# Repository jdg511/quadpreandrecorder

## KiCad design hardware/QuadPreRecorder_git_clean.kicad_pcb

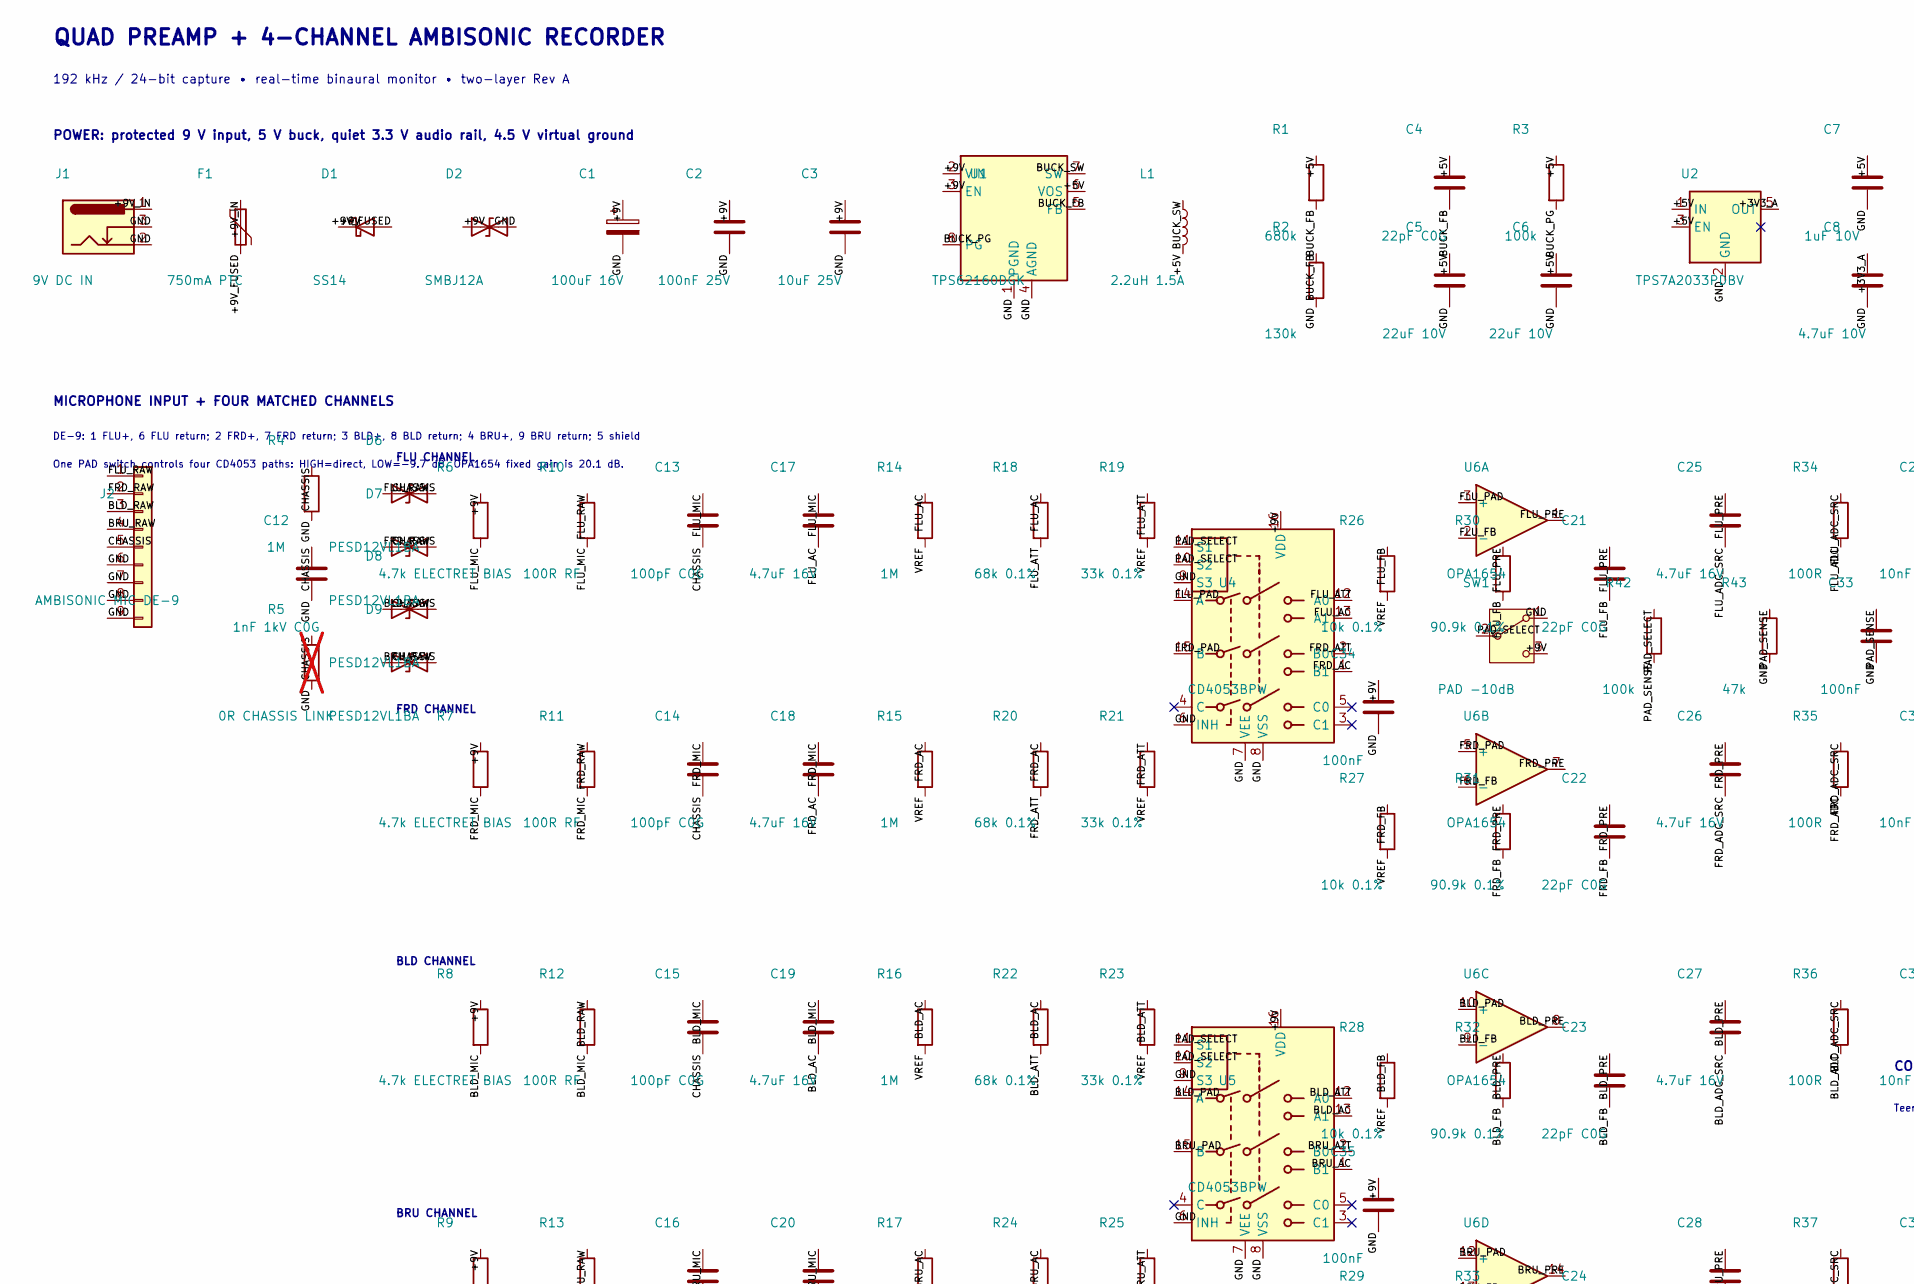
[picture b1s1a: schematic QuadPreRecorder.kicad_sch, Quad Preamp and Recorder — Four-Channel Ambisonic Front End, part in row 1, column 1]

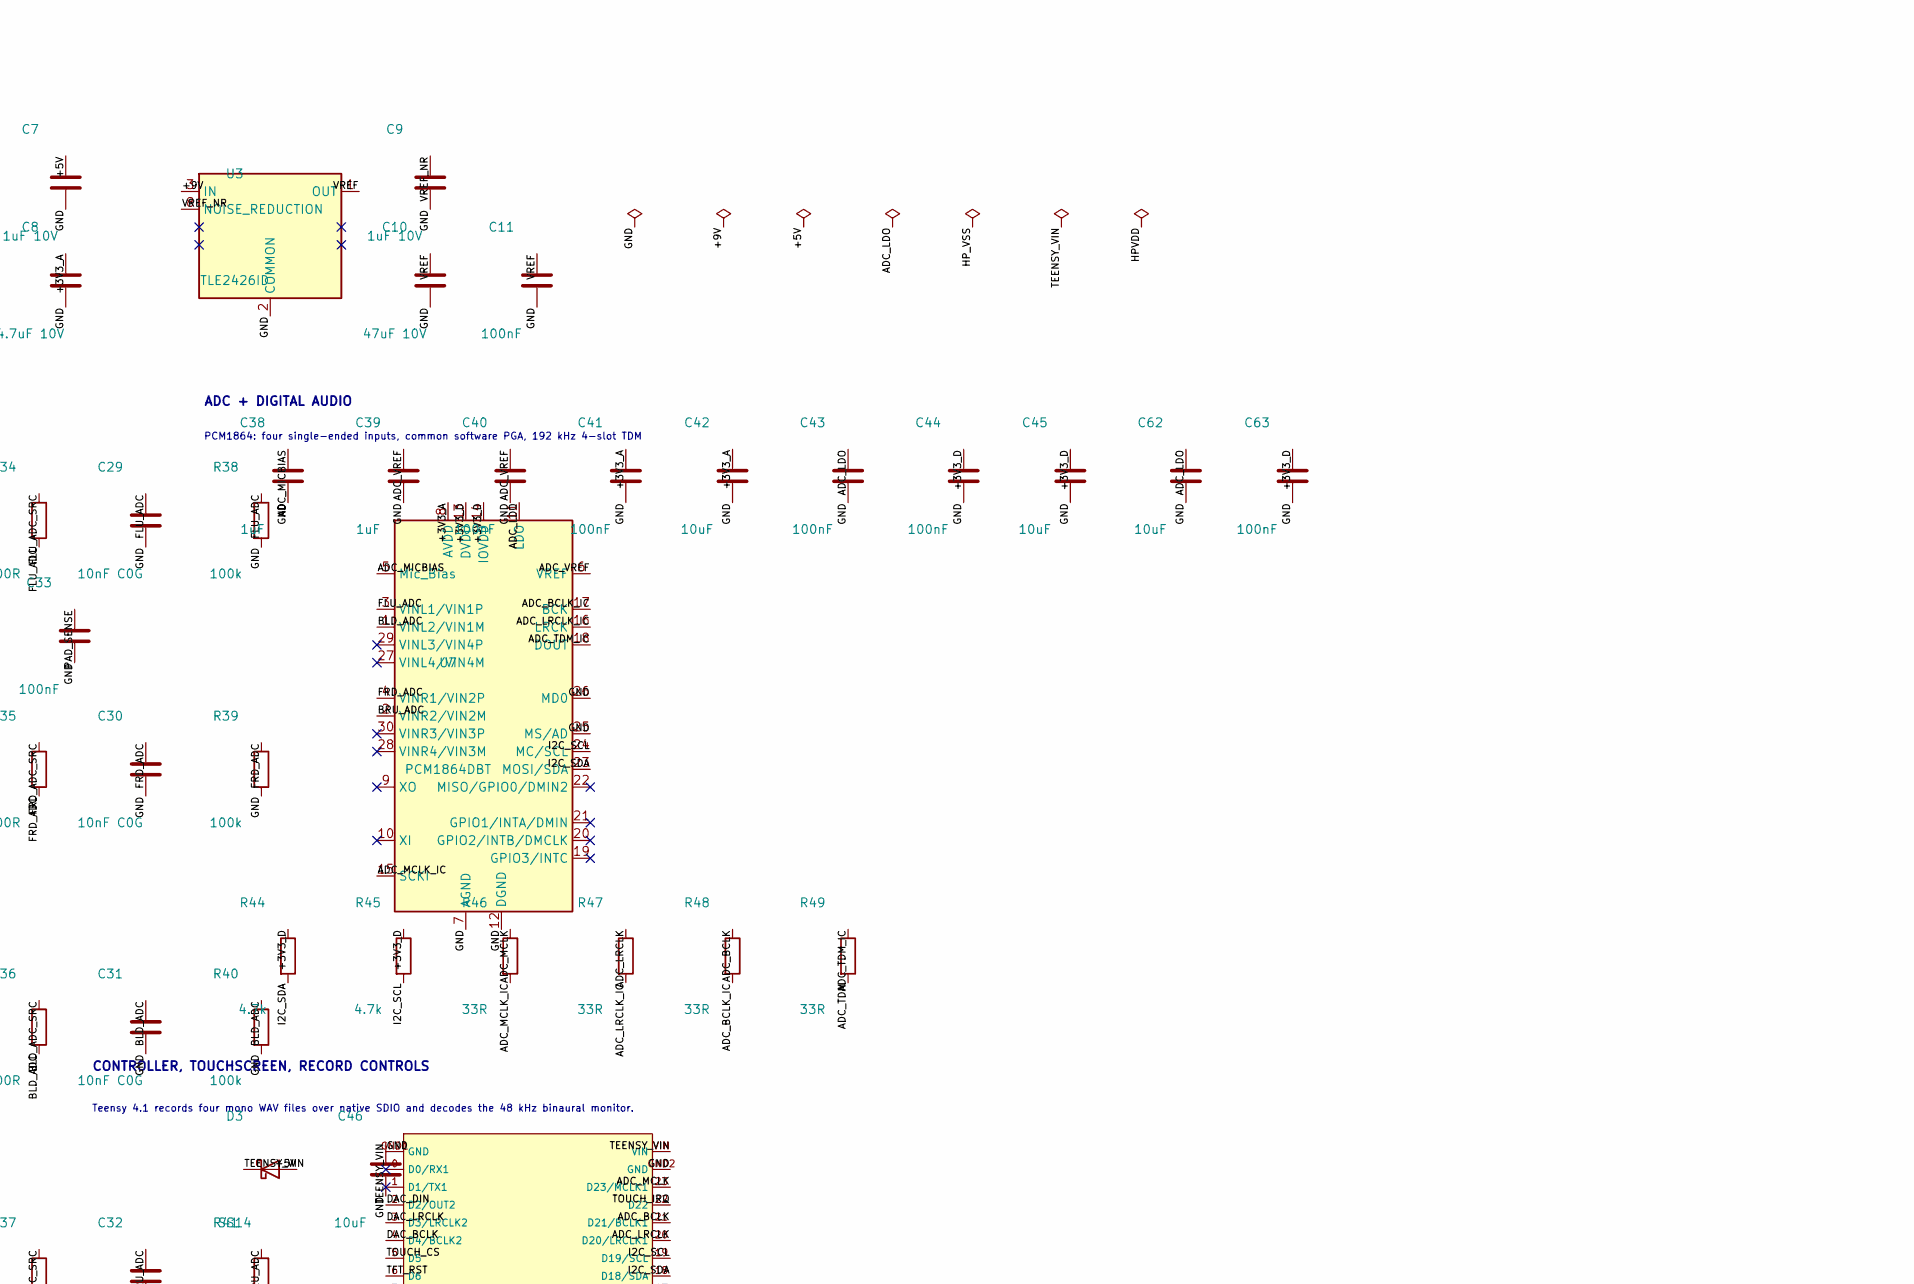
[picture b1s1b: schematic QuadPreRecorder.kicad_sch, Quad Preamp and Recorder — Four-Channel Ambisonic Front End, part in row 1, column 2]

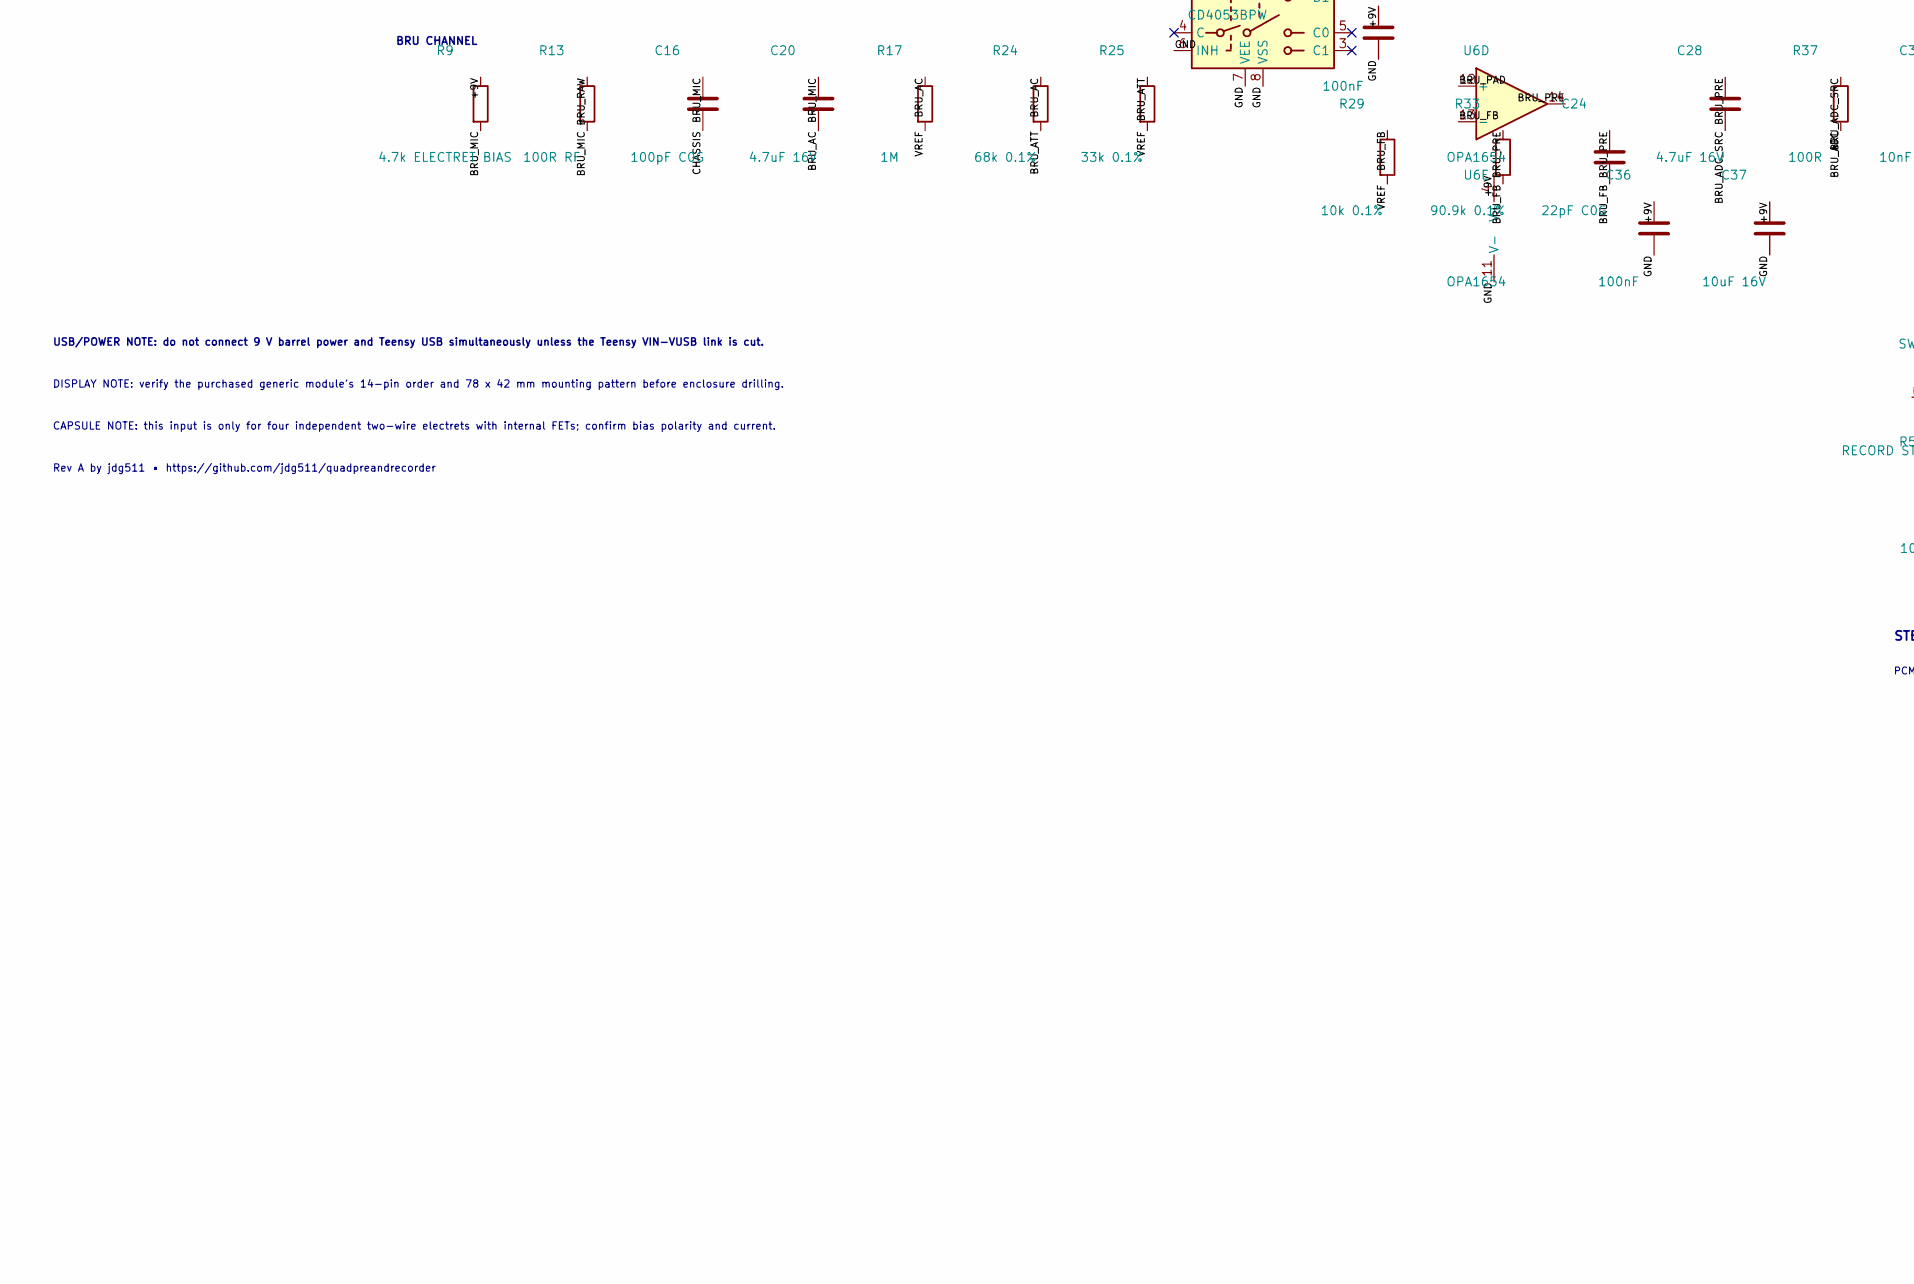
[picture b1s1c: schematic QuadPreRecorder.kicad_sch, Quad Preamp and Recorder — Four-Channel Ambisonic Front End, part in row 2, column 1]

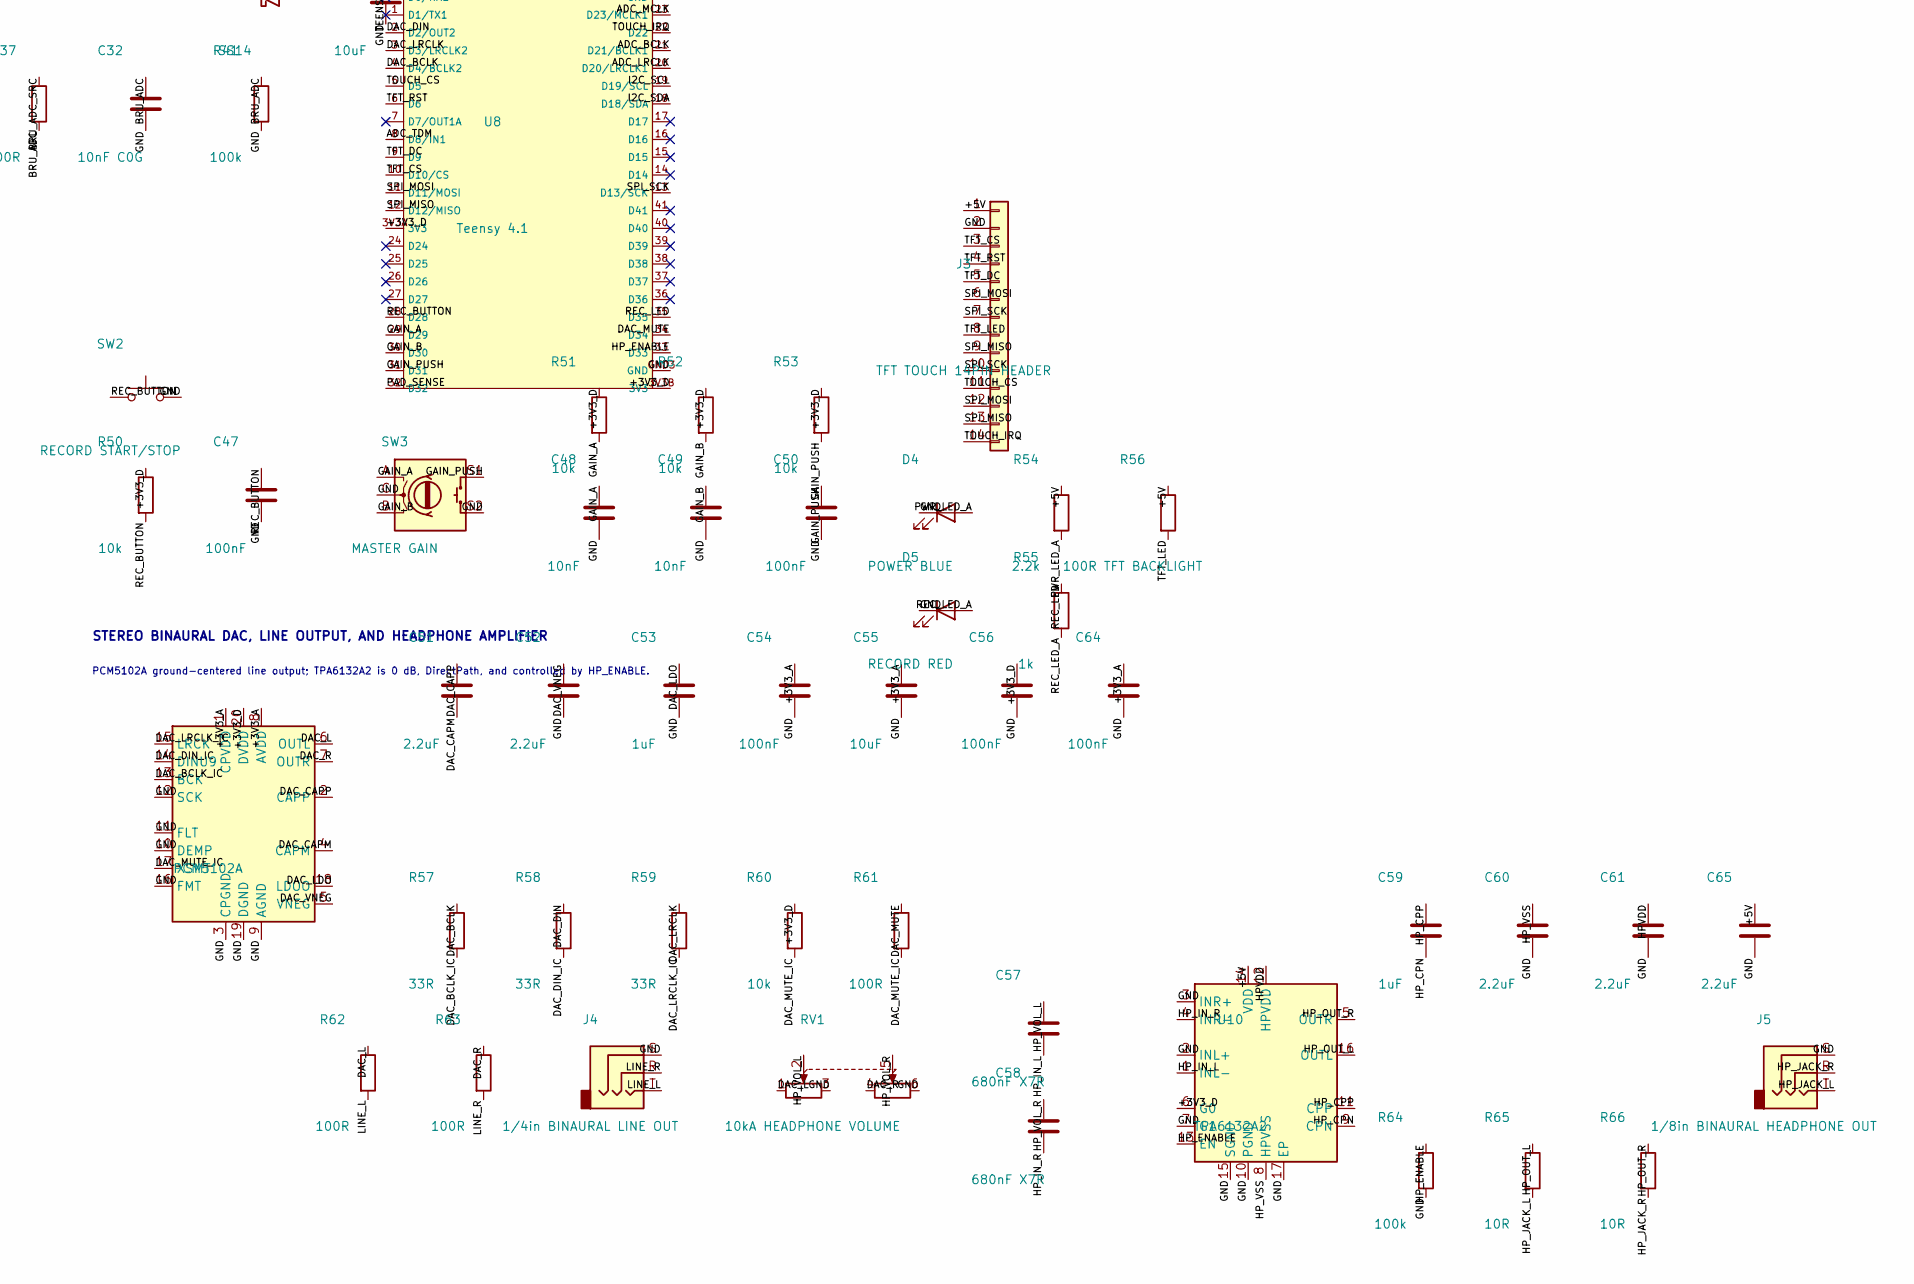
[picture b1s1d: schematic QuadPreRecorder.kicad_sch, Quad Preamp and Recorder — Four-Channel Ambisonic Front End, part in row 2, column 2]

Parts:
C1: 100uF 16V; CP_Elec_6.3x5.8; MPN EEE-FK series low-ESR aluminium electro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
C2: 100nF 25V; C_0805_2012Metric; MPN GRM series X7R/C0G
C3: 10uF 25V; C_1206_3216Metric; MPN GRM series X7R/C0G
C4, C21, C22, C23, C24: 22pF C0G; C_0603_1608Metric; MPN GRM series X7R/C0G
C5, C6: 22uF 10V; C_1206_3216Metric; MPN GRM series X7R/C0G
C7, C9: 1uF 10V; C_0805_2012Metric; MPN GRM series X7R/C0G
C8: 4.7uF 10V; C_0805_2012Metric; MPN GRM series X7R/C0G
C10: 47uF 10V; C_1206_3216Metric; MPN GRM series X7R/C0G
C11, C33, C34, C35, C36, C40, C41, C43, C44, C47, C50, C54, C56, C63, C64: 100nF; C_0603_1608Metric; MPN GRM series X7R/C0G
C12: 1nF 1kV C0G; C_0805_2012Metric; MPN GRM series X7R/C0G
C13, C14, C15, C16: 100pF C0G; C_0603_1608Metric; MPN GRM series X7R/C0G
C17, C18, C19, C20, C25, C26, C27, C28: 4.7uF 16V; C_1206_3216Metric; MPN GRM series X7R/C0G
C29, C30, C31, C32: 10nF C0G; C_0603_1608Metric; MPN GRM series X7R/C0G
C37: 10uF 16V; C_1206_3216Metric; MPN GRM series X7R/C0G
C38, C39, C53, C59: 1uF; C_0805_2012Metric; MPN GRM series X7R/C0G
C42, C45, C46, C55, C62: 10uF; C_1206_3216Metric; MPN GRM series X7R/C0G
C48, C49: 10nF; C_0603_1608Metric; MPN GRM series X7R/C0G
C51, C52, C60, C61, C65: 2.2uF; C_0805_2012Metric; MPN GRM series X7R/C0G
C57, C58: 680nF X7R; C_0805_2012Metric; MPN GRM series X7R/C0G
D1, D3: SS14; D_SMA; MPN SS14-13-F
D2: SMBJ12A; D_SMB; MPN SMBJ12A
D4: POWER BLUE; LED_0603_1608Metric; MPN LTST-C190TBKT
D5: RECORD RED; LED_0603_1608Metric; MPN LTST-C190KRKT
D6, D7, D8, D9: PESD12VL1BA; D_SOD-323; MPN PESD12VL1BA,115
F1: 750mA PTC; Fuse_1206_3216Metric; MPN 1206L075/13.2WR
J1: 9V DC IN; BarrelJack_CUI_PJ-102AH_Horizontal; MPN PJ-102AH
J2: AMBISONIC MIC DE-9; DSUB-9_Socket_Horizontal_P2.77x2.84mm_EdgePinOffset9.40mm; MPN LD09S13A4GV00LF
J3: TFT TOUCH 14PIN HEADER; PinHeader_1x14_P2.54mm_Vertical; MPN PRPC014SAAN-RC
J4: 1/4in BINAURAL LINE OUT; Jack_6.35mm_Neutrik_NRJ6HF_Horizontal; MPN NRJ6HF
J5: 1/8in BINAURAL HEADPHONE OUT; Jack_3.5mm_CUI_SJ1-3533NG_Horizontal; MPN SJ1-3533NG
L1: 2.2uH 1.5A; L_Abracon_ASPIAIG-F4020; MPN ASPIAIG-F4020-2R2M-T
R1: 680k; R_0603_1608Metric; MPN RC0603FR series, 1%
R2: 130k; R_0603_1608Metric; MPN RC0603FR series, 1%
R3, R38, R39, R40, R41, R42, R64: 100k; R_0603_1608Metric; MPN RC0603FR series, 1%
R4, R14, R15, R16, R17: 1M; R_0603_1608Metric; MPN RC0603FR series, 1%
R5: 0R CHASSIS LINK; R_0603_1608Metric; MPN RC0603FR series, 1%; not fitted
R6, R7, R8, R9: 4.7k ELECTRET BIAS; R_0603_1608Metric; MPN RC0603FR series, 1%
R10, R11, R12, R13: 100R RF; R_0603_1608Metric; MPN RC0603FR series, 1%
R18, R20, R22, R24: 68k 0.1%; R_0603_1608Metric; MPN TNPW0603 series, 0.1%
R19, R21, R23, R25: 33k 0.1%; R_0603_1608Metric; MPN TNPW0603 series, 0.1%
R26, R27, R28, R29: 10k 0.1%; R_0603_1608Metric; MPN TNPW0603 series, 0.1%
R30, R31, R32, R33: 90.9k 0.1%; R_0603_1608Metric; MPN TNPW0603 series, 0.1%
R34, R35, R36, R37, R61, R62, R63: 100R; R_0603_1608Metric; MPN RC0603FR series, 1%
R43: 47k; R_0603_1608Metric; MPN RC0603FR series, 1%
R44, R45: 4.7k; R_0603_1608Metric; MPN RC0603FR series, 1%
R46, R47, R48, R49, R57, R58, R59: 33R; R_0603_1608Metric; MPN RC0603FR series, 1%
R50, R51, R52, R53, R60: 10k; R_0603_1608Metric; MPN RC0603FR series, 1%
R54: 2.2k; R_0603_1608Metric; MPN RC0603FR series, 1%
R55: 1k; R_0603_1608Metric; MPN RC0603FR series, 1%
R56: 100R TFT BACKLIGHT; R_0805_2012Metric; MPN RC0805FR-07100RL
R65, R66: 10R; R_0603_1608Metric; MPN RC0603FR series, 1%
RV1: 10kA HEADPHONE VOLUME; RK097_Dual_Horizontal_NoEdgeGuide; MPN RK0971221-F15-C0-A103
SW1: PAD -10dB; SW_Slide_SPDT_Straight_CK_OS102011MS2Q; MPN OS102011MS2QN1
SW2: RECORD START/STOP; SW_PUSH-12mm; MPN B3F-4050
SW3: MASTER GAIN; RotaryEncoder_Alps_EC11E-Switch_Vertical_H20mm; MPN EC11E15244G1
U1: TPS62160DGK; VSSOP-8_3x3mm_P0.65mm; MPN TPS62160DGKR
U2: TPS7A2033PDBV; SOT-23-5; MPN TPS7A2033PDBVR
U3: TLE2426ID; SOIC-8_3.9x4.9mm_P1.27mm; MPN TLE2426IDR
U4, U5: CD4053BPW; TSSOP-16_4.4x5mm_P0.65mm; MPN CD4053BPWR
U6: OPA1654; TSSOP-14_4.4x5mm_P0.65mm; MPN OPA1654AIPWR
U7: PCM1864DBT; TSSOP-30_4.4x7.8mm_P0.5mm; MPN PCM1864DBTR
U8: Teensy 4.1; Teensy41_Socket; MPN TEENSY41
U9: PCM5102A; TSSOP-20_4.4x6.5mm_P0.65mm; MPN PCM5102APWR
U10: TPA6132A2; WQFN-16-1EP_3x3mm_P0.5mm_EP1.6x1.6mm; MPN TPA6132A2RTER

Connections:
/+3V3_A: C8.1, C41.1, C42.1, C54.1, C55.1, C64.1, U2.5 (OUT), U7.8 (AVDD), U9.1 (CPVDD), U9.8 (AVDD)
/+3V3_D: C44.1, C45.1, C56.1, C63.1, R44.1, R45.1, R50.1, R51.1, R52.1, R53.1, R60.1, U7.13 (DVDD), U7.14 (IOVDD), U8.3V3A (3V3), U8.3V3B (3V3), U9.20 (DVDD), U10.6 (G0)
/+5V: C4.1, C5.1, C6.1, C7.1, C65.1, D3.2 (A), J3.1, L1.2, R1.1, R3.1, R54.1, R56.1, U1.6 (VOS), U2.1 (IN), U2.3 (EN), U10.14 (VDD)
/+9V: C1.1, C2.1, C3.1, C34.1, C35.1, C36.1, C37.1, D1.1 (K), D2.1 (A1), R6.1, R7.1, R8.1, R9.1, SW1.3 (C), U1.2 (VIN), U1.3 (EN), U3.3 (IN), U4.16 (VDD), U5.16 (VDD), U6.4 (V+)
/+9V_FUSED: D1.2 (A), F1.2
/+9V_IN: F1.1, J1.1
/ADC_BCLK: R48.1, U8.21 (D21/BCLK1)
/ADC_BCLK_IC: R48.2, U7.17 (BCK)
/ADC_LDO: C43.1, C62.1, U7.11 (LDO)
/ADC_LRCLK: R47.1, U8.20 (D20/LRCLK1)
/ADC_LRCLK_IC: R47.2, U7.16 (LRCK)
/ADC_MCLK: R46.1, U8.23 (D23/MCLK1)
/ADC_MCLK_IC: R46.2, U7.15 (SCKI)
/ADC_MICBIAS: C38.1, U7.5 (Mic_Bias)
/ADC_TDM: R49.2, U8.8 (D8/IN1)
/ADC_TDM_IC: R49.1, U7.18 (DOUT)
/ADC_VREF: C39.1, C40.1, U7.6 (VREF)
/BLD_AC: C19.2, R16.1, R22.1, U5.13 (A1)
/BLD_ADC: C31.1, R36.2, R40.1, U7.1 (VINL2/VIN1M)
/BLD_ADC_SRC: C27.2, R36.1
/BLD_ATT: R22.2, R23.1, U5.12 (A0)
/BLD_FB: C23.2, R28.1, R32.2, U6.9 (-)
/BLD_MIC: C15.1, C19.1, R8.2, R12.2
/BLD_PAD: U5.14 (A), U6.10 (+)
/BLD_PRE: C23.1, C27.1, R32.1, U6.8
/BLD_RAW: D8.1 (A1), J2.3, R12.1
/BRU_AC: C20.2, R17.1, R24.1, U5.1 (B1)
/BRU_ADC: C32.1, R37.2, R41.1, U7.2 (VINR2/VIN2M)
/BRU_ADC_SRC: C28.2, R37.1
/BRU_ATT: R24.2, R25.1, U5.2 (B0)
/BRU_FB: C24.2, R29.1, R33.2, U6.13 (-)
/BRU_MIC: C16.1, C20.1, R9.2, R13.2
/BRU_PAD: U5.15 (B), U6.12 (+)
/BRU_PRE: C24.1, C28.1, R33.1, U6.14
/BRU_RAW: D9.1 (A1), J2.4, R13.1
/BUCK_FB: C4.2, R1.2, R2.1, U1.5 (FB)
/BUCK_PG: R3.2, U1.8 (PG)
/BUCK_SW: L1.1, U1.7 (SW)
/CHASSIS: C12.1, C13.2, C14.2, C15.2, C16.2, D6.2 (A2), D7.2 (A2), D8.2 (A2), D9.2 (A2), J2.5, R4.1, R5.1
/DAC_BCLK: R57.1, U8.4 (D4/BCLK2)
/DAC_BCLK_IC: R57.2, U9.13 (BCK)
/DAC_CAPM: C51.2, U9.4 (CAPM)
/DAC_CAPP: C51.1, U9.2 (CAPP)
/DAC_DIN: R58.1, U8.2 (D2/OUT2)
/DAC_DIN_IC: R58.2, U9.14 (DIN)
/DAC_L: R62.1, RV1.1, U9.6 (OUTL)
/DAC_LDO: C53.1, U9.18 (LDOO)
/DAC_LRCLK: R59.1, U8.3 (D3/LRCLK2)
/DAC_LRCLK_IC: R59.2, U9.15 (LRCK)
/DAC_MUTE: R61.1, U8.34 (D34)
/DAC_MUTE_IC: R60.2, R61.2, U9.17 (XSMT)
/DAC_R: R63.1, RV1.4, U9.7 (OUTR)
/DAC_VNEG: C52.1, U9.5 (VNEG)
/FLU_AC: C17.2, R14.1, R18.1, U4.13 (A1)
/FLU_ADC: C29.1, R34.2, R38.1, U7.3 (VINL1/VIN1P)
/FLU_ADC_SRC: C25.2, R34.1
/FLU_ATT: R18.2, R19.1, U4.12 (A0)
/FLU_FB: C21.2, R26.1, R30.2, U6.2 (-)
/FLU_MIC: C13.1, C17.1, R6.2, R10.2
/FLU_PAD: U4.14 (A), U6.3 (+)
/FLU_PRE: C21.1, C25.1, R30.1, U6.1
/FLU_RAW: D6.1 (A1), J2.1, R10.1
/FRD_AC: C18.2, R15.1, R20.1, U4.1 (B1)
/FRD_ADC: C30.1, R35.2, R39.1, U7.4 (VINR1/VIN2P)
/FRD_ADC_SRC: C26.2, R35.1
/FRD_ATT: R20.2, R21.1, U4.2 (B0)
/FRD_FB: C22.2, R27.1, R31.2, U6.6 (-)
/FRD_MIC: C14.1, C18.1, R7.2, R11.2
/FRD_PAD: U4.15 (B), U6.5 (+)
/FRD_PRE: C22.1, C26.1, R31.1, U6.7
/FRD_RAW: D7.1 (A1), J2.2, R11.1
/GAIN_A: C48.1, R51.2, SW3.A, U8.29 (D29)
/GAIN_B: C49.1, R52.2, SW3.B, U8.30 (D30)
/GAIN_PUSH: C50.1, R53.2, SW3.S1, U8.31 (D31)
/GND: C1.2, C2.2, C3.2, C5.2, C6.2, C7.2, C8.2, C9.2, C10.2, C11.2, C12.2, C29.2, C30.2, C31.2, C32.2, C33.2, C34.2, C35.2, C36.2, C37.2, C38.2, C39.2, C40.2, C41.2, C42.2, C43.2, C44.2, C45.2, C46.2, C47.2, C48.2, C49.2, C50.2, C52.2, C53.2, C54.2, C55.2, C56.2, C60.2, C61.2, C62.2, C63.2, C64.2, C65.2, D2.2 (A2), D4.1 (K), D5.1 (K), J1.2, J1.3, J2.6, J2.7, J2.8, J2.9, J3.2, J4.S, J5.S, R2.2, R4.2, R5.2, R38.2, R39.2, R40.2, R41.2, R43.2, R64.2, RV1.3, RV1.6, SW1.1 (A), SW2.2, SW3.C, SW3.S2, U1.1 (PGND), U1.4 (AGND), U2.2 (GND), U3.2 (COMMON), U4.6 (INH), U4.7 (VEE), U4.8 (VSS), U4.9 (S3), U5.6 (INH), U5.7 (VEE), U5.8 (VSS), U5.9 (S3), U6.11 (V-), U7.7 (AGND), U7.12 (DGND), U7.25 (MS/AD), U7.26 (MD0), U8.GND1 (GND), U8.GND2 (GND), U8.GND3 (GND), U9.3 (CPGND), U9.9 (AGND), U9.10 (DEMP), U9.11 (FLT), U9.12 (SCK), U9.16 (FMT), U9.19 (DGND), U10.2 (INL+), U10.3 (INR+), U10.7 (G1), U10.10 (PGND), U10.15 (SGND), U10.17 (EP)
/HPVDD: C61.1, U10.12 (HPVDD)
/HP_CPN: C59.2, U10.9 (CPN)
/HP_CPP: C59.1, U10.11 (CPP)
/HP_ENABLE: R64.1, U8.33 (D33), U10.13 (EN)
/HP_IN_L: C57.2, U10.1 (INL-)
/HP_IN_R: C58.2, U10.4 (INR-)
/HP_JACK_L: J5.T, R65.2
/HP_JACK_R: J5.R, R66.2
/HP_OUT_L: R65.1, U10.16 (OUTL)
/HP_OUT_R: R66.1, U10.5 (OUTR)
/HP_VOL_L: C57.1, RV1.2
/HP_VOL_R: C58.1, RV1.5
/HP_VSS: C60.1, U10.8 (HPVSS)
/I2C_SCL: R45.2, U7.24 (MC/SCL), U8.19 (D19/SCL)
/I2C_SDA: R44.2, U7.23 (MOSI/SDA), U8.18 (D18/SDA)
/LINE_L: J4.T, R62.2
/LINE_R: J4.R, R63.2
/PAD_SELECT: R42.1, SW1.2 (B), U4.10 (S2), U4.11 (S1), U5.10 (S2), U5.11 (S1)
/PAD_SENSE: C33.1, R42.2, R43.1, U8.32 (D32)
/PWR_LED_A: D4.2 (A), R54.2
/REC_BUTTON: C47.1, R50.2, SW2.1, U8.28 (D28)
/REC_LED: R55.1, U8.35 (D35)
/REC_LED_A: D5.2 (A), R55.2
/SPI_MISO: J3.9, J3.13, U8.12 (D12/MISO)
/SPI_MOSI: J3.6, J3.12, U8.11 (D11/MOSI)
/SPI_SCK: J3.7, J3.10, U8.13 (D13/SCK)
/TEENSY_VIN: C46.1, D3.1 (K), U8.VIN
/TFT_CS: J3.3, U8.10 (D10/CS)
/TFT_DC: J3.5, U8.9 (D9)
/TFT_LED: J3.8, R56.2
/TFT_RST: J3.4, U8.6 (D6)
/TOUCH_CS: J3.11, U8.5 (D5)
/TOUCH_IRQ: J3.14, U8.22 (D22)
/VREF: C10.1, C11.1, R14.2, R15.2, R16.2, R17.2, R19.2, R21.2, R23.2, R25.2, R26.2, R27.2, R28.2, R29.2, U3.1 (OUT)
/VREF_NR: C9.1, U3.8 (NOISE_REDUCTION)

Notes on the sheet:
QUAD PREAMP + 4-CHANNEL AMBISONIC RECORDER
192 kHz / 24-bit capture • real-time binaural monitor • two-layer Rev A
POWER: protected 9 V input, 5 V buck, quiet 3.3 V audio rail, 4.5 V virtual ground
MICROPHONE INPUT + FOUR MATCHED CHANNELS
DE-9: 1 FLU+, 6 FLU return; 2 FRD+, 7 FRD return; 3 BLD+, 8 BLD return; 4 BRU+, 9 BRU return; 5 shield
One PAD switch controls four CD4053 paths: HIGH=direct, LOW=-9.7 dB. OPA1654 fixed gain is 20.1 dB.
FLU CHANNEL
FRD CHANNEL
BLD CHANNEL
BRU CHANNEL
ADC + DIGITAL AUDIO
PCM1864: four single-ended inputs, common software PGA, 192 kHz 4-slot TDM
CONTROLLER, TOUCHSCREEN, RECORD CONTROLS
Teensy 4.1 records four mono WAV files over native SDIO and decodes the 48 kHz binaural monitor.
STEREO BINAURAL DAC, LINE OUTPUT, AND HEADPHONE AMPLIFIER
PCM5102A ground-centered line output; TPA6132A2 is 0 dB, DirectPath, and controlled by HP_ENABLE.
USB/POWER NOTE: do not connect 9 V barrel power and Teensy USB simultaneously unless the Teensy VIN-VUSB link is cut.
DISPLAY NOTE: verify the purchased generic module's 14-pin order and 78 x 42 mm mounting pattern before enclosure drilling.
CAPSULE NOTE: this input is only for four independent two-wire electrets with internal FETs; confirm bias polarity and current.
Rev A by jdg511 • https://github.com/jdg511/quadpreandrecorder

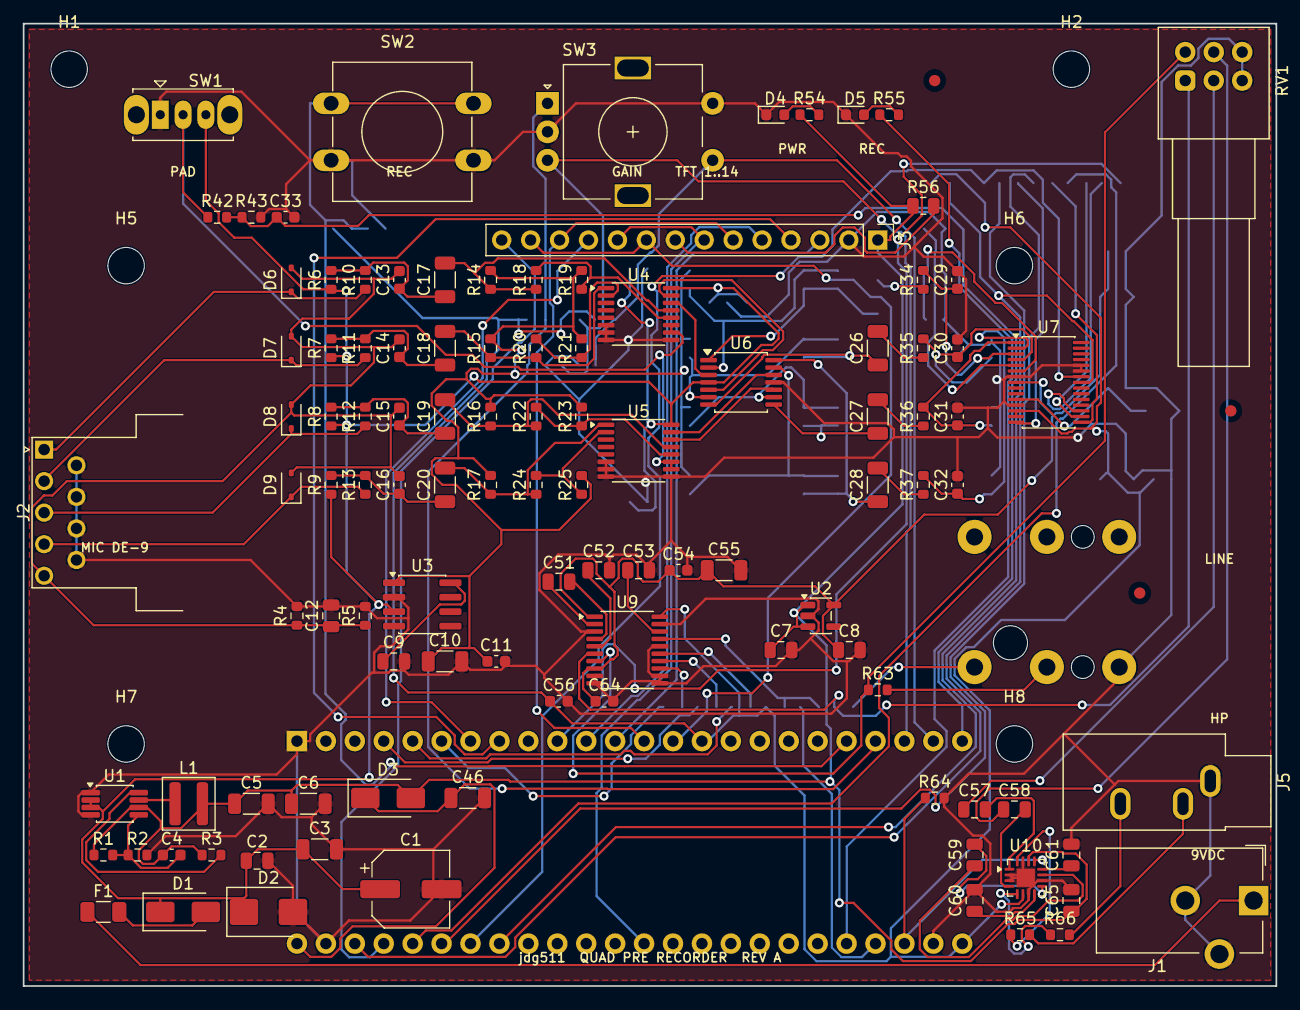
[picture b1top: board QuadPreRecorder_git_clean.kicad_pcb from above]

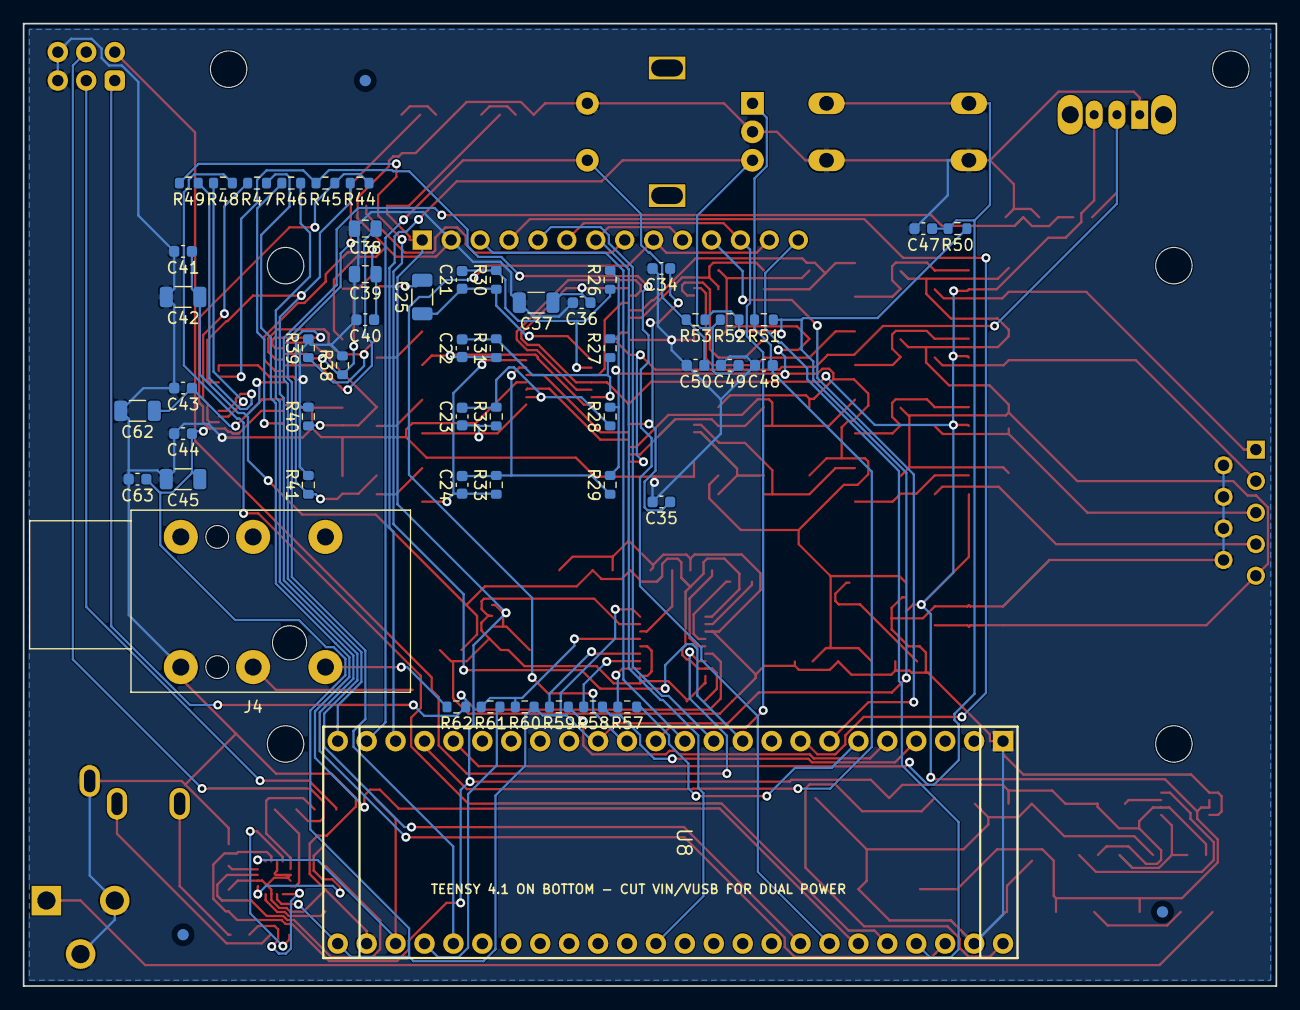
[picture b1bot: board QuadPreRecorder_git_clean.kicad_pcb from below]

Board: 2 copper layers, 110.0 x 84.5 mm, 173 parts (56 on the bottom side), 110 nets.

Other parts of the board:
FID1, FID2, FID3, FID4, FID5, FID6: Fiducial 1mm; Fiducial_1mm_Mask2mm
H1, H2: M3 PCB; MountingHole_3.2mm_M3
H5, H6, H7, H8: M3 TFT 78x42; MountingHole_3.2mm_M3

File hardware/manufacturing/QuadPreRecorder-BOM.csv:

"Designator","Comment","Footprint","Manufacturer","Manufacturer Part Number","Datasheet","Quantity","DNP"
"C1","100uF 16V","Capacitor_SMD:CP_Elec_6.3x5.8","Panasonic","EEE-FK series low-ESR aluminium electrolytic","","1",""
"C2","100nF 25V","Capacitor_SMD:C_0805_2012Metric","Murata","GRM series X7R/C0G","","1",""
"C3","10uF 25V","Capacitor_SMD:C_1206_3216Metric","Murata","GRM series X7R/C0G","","1",""
"C4,C21-C24","22pF C0G","Capacitor_SMD:C_0603_1608Metric","Murata","GRM series X7R/C0G","","5",""
"C5,C6","22uF 10V","Capacitor_SMD:C_1206_3216Metric","Murata","GRM series X7R/C0G","","2",""
"C7,C9","1uF 10V","Capacitor_SMD:C_0805_2012Metric","Murata","GRM series X7R/C0G","","2",""
"C8","4.7uF 10V","Capacitor_SMD:C_0805_2012Metric","Murata","GRM series X7R/C0G","","1",""
"C10","47uF 10V","Capacitor_SMD:C_1206_3216Metric","Murata","GRM series X7R/C0G","","1",""
"C11,C33-C36,C40,C41,C43,C44,C47,C50,C54,C56,C63,C64","100nF","Capacitor_SMD:C_0603_1608Metric","Murata","GRM series X7R/C0G","","15",""
"C12","1nF 1kV C0G","Capacitor_SMD:C_0805_2012Metric","Murata","GRM series X7R/C0G","","1",""
"C13-C16","100pF C0G","Capacitor_SMD:C_0603_1608Metric","Murata","GRM series X7R/C0G","","4",""
"C17-C20,C25-C28","4.7uF 16V","Capacitor_SMD:C_1206_3216Metric","Murata","GRM series X7R/C0G","","8",""
"C29-C32","10nF C0G","Capacitor_SMD:C_0603_1608Metric","Murata","GRM series X7R/C0G","","4",""
"C37","10uF 16V","Capacitor_SMD:C_1206_3216Metric","Murata","GRM series X7R/C0G","","1",""
"C38,C39,C53,C59","1uF","Capacitor_SMD:C_0805_2012Metric","Murata","GRM series X7R/C0G","","4",""
"C42,C45,C46,C55,C62","10uF","Capacitor_SMD:C_1206_3216Metric","Murata","GRM series X7R/C0G","","5",""
"C48,C49","10nF","Capacitor_SMD:C_0603_1608Metric","Murata","GRM series X7R/C0G","","2",""
"C51,C52,C60,C61,C65","2.2uF","Capacitor_SMD:C_0805_2012Metric","Murata","GRM series X7R/C0G","","5",""
"C57,C58","680nF X7R","Capacitor_SMD:C_0805_2012Metric","Murata","GRM series X7R/C0G","","2",""
"D1,D3","SS14","Diode_SMD:D_SMA","Diodes Incorporated","SS14-13-F","","2",""
"D2","SMBJ12A","Diode_SMD:D_SMB","Littelfuse","SMBJ12A","","1",""
"D4","POWER BLUE","LED_SMD:LED_0603_1608Metric","Lite-On","LTST-C190TBKT","","1",""
"D5","RECORD RED","LED_SMD:LED_0603_1608Metric","Lite-On","LTST-C190KRKT","","1",""
"D6-D9","PESD12VL1BA","Diode_SMD:D_SOD-323","Nexperia","PESD12VL1BA,115","https://assets.nexperia.com/documents/data-sheet/PESD12VL1BA.pdf","4",""
"F1","750mA PTC","Fuse:Fuse_1206_3216Metric","Littelfuse","1206L075/13.2WR","","1",""
"J1","9V DC IN","Connector_BarrelJack:BarrelJack_CUI_PJ-102AH_Horizontal","CUI Devices","PJ-102AH","","1",""
"J2","AMBISONIC MIC DE-9","Connector_Dsub:DSUB-9_Socket_Horizontal_P2.77x2.84mm_EdgePinOffset9.40mm","Amphenol ICC","LD09S13A4GV00LF","","1",""
"J3","TFT TOUCH 14PIN HEADER","Connector_PinHeader_2.54mm:PinHeader_1x14_P2.54mm_Vertical","Sullins Connector Solutions","PRPC014SAAN-RC","","1",""
"J4","1/4in BINAURAL LINE OUT","Connector_Audio:Jack_6.35mm_Neutrik_NRJ6HF_Horizontal","Neutrik","NRJ6HF","","1",""
"J5","1/8in BINAURAL HEADPHONE OUT","Connector_Audio:Jack_3.5mm_CUI_SJ1-3533NG_Horizontal","CUI Devices","SJ1-3533NG","","1",""
"L1","2.2uH 1.5A","Inductor_SMD:L_Abracon_ASPIAIG-F4020","Abracon","ASPIAIG-F4020-2R2M-T","","1",""
"R1","680k","Resistor_SMD:R_0603_1608Metric","Yageo","RC0603FR series, 1%","","1",""
"R2","130k","Resistor_SMD:R_0603_1608Metric","Yageo","RC0603FR series, 1%","","1",""
"R3,R38-R42,R64","100k","Resistor_SMD:R_0603_1608Metric","Yageo","RC0603FR series, 1%","","7",""
"R4,R14-R17","1M","Resistor_SMD:R_0603_1608Metric","Yageo","RC0603FR series, 1%","","5",""
"R5","0R CHASSIS LINK","Resistor_SMD:R_0603_1608Metric","Yageo","RC0603FR series, 1%","","1","DNP"
"R6-R9","4.7k ELECTRET BIAS","Resistor_SMD:R_0603_1608Metric","Yageo","RC0603FR series, 1%","","4",""
"R10-R13","100R RF","Resistor_SMD:R_0603_1608Metric","Yageo","RC0603FR series, 1%","","4",""
"R18,R20,R22,R24","68k 0.1%","Resistor_SMD:R_0603_1608Metric","Vishay","TNPW0603 series, 0.1%","","4",""
"R19,R21,R23,R25","33k 0.1%","Resistor_SMD:R_0603_1608Metric","Vishay","TNPW0603 series, 0.1%","","4",""
"R26-R29","10k 0.1%","Resistor_SMD:R_0603_1608Metric","Vishay","TNPW0603 series, 0.1%","","4",""
"R30-R33","90.9k 0.1%","Resistor_SMD:R_0603_1608Metric","Vishay","TNPW0603 series, 0.1%","","4",""
"R34-R37,R61-R63","100R","Resistor_SMD:R_0603_1608Metric","Yageo","RC0603FR series, 1%","","7",""
"R43","47k","Resistor_SMD:R_0603_1608Metric","Yageo","RC0603FR series, 1%","","1",""
"R44,R45","4.7k","Resistor_SMD:R_0603_1608Metric","Yageo","RC0603FR series, 1%","","2",""
"R46-R49,R57-R59","33R","Resistor_SMD:R_0603_1608Metric","Yageo","RC0603FR series, 1%","","7",""
"R50-R53,R60","10k","Resistor_SMD:R_0603_1608Metric","Yageo","RC0603FR series, 1%","","5",""
"R54","2.2k","Resistor_SMD:R_0603_1608Metric","Yageo","RC0603FR series, 1%","","1",""
"R55","1k","Resistor_SMD:R_0603_1608Metric","Yageo","RC0603FR series, 1%","","1",""
"R56","100R TFT BACKLIGHT","Resistor_SMD:R_0805_2012Metric","Yageo","RC0805FR-07100RL","","1",""
"R65,R66","10R","Resistor_SMD:R_0603_1608Metric","Yageo","RC0603FR series, 1%","","2",""
"RV1","10kA HEADPHONE VOLUME","QuadPreRecorder:RK097_Dual_Horizontal_NoEdgeGuide","Alps Alpine","RK0971221-F15-C0-A103","","1",""
"SW1","PAD -10dB","Button_Switch_THT:SW_Slide_SPDT_Straight_CK_OS102011MS2Q","C&K","OS102011MS2QN1","","1",""
"SW2","RECORD START/STOP","Button_Switch_THT:SW_PUSH-12mm","Omron","B3F-4050","","1",""
"SW3","MASTER GAIN","Rotary_Encoder:RotaryEncoder_Alps_EC11E-Switch_Vertical_H20mm","Alps Alpine","EC11E15244G1","","1",""
"U1","TPS62160DGK","Package_SO:VSSOP-8_3x3mm_P0.65mm","Texas Instruments","TPS62160DGKR","https://www.ti.com/lit/ds/symlink/tps62160.pdf","1",""
"U2","TPS7A2033PDBV","Package_TO_SOT_SMD:SOT-23-5","Texas Instruments","TPS7A2033PDBVR","https://www.ti.com/lit/ds/symlink/tps7a20.pdf","1",""
"U3","TLE2426ID","Package_SO:SOIC-8_3.9x4.9mm_P1.27mm","Texas Instruments","TLE2426IDR","https://www.ti.com/lit/ds/symlink/tle2426.pdf","1",""
"U4,U5","CD4053BPW","Package_SO:TSSOP-16_4.4x5mm_P0.65mm","Texas Instruments","CD4053BPWR","https://www.ti.com/lit/ds/symlink/cd4053b.pdf","2",""
"U6","OPA1654","Package_SO:TSSOP-14_4.4x5mm_P0.65mm","Texas Instruments","OPA1654AIPWR","https://www.ti.com/lit/ds/symlink/opa1654.pdf","1",""
"U7","PCM1864DBT","Package_SO:TSSOP-30_4.4x7.8mm_P0.5mm","Texas Instruments","PCM1864DBTR","https://www.ti.com/lit/ds/symlink/pcm1864.pdf","1",""
"U8","Teensy 4.1","QuadPreRecorder:Teensy41_Socket","PJRC","TEENSY41","https://www.pjrc.com/store/teensy41.html","1",""
"U9","PCM5102A","Package_SO:TSSOP-20_4.4x6.5mm_P0.65mm","Texas Instruments","PCM5102APWR","https://www.ti.com/lit/ds/symlink/pcm5102a.pdf","1",""
"U10","TPA6132A2","Package_DFN_QFN:WQFN-16-1EP_3x3mm_P0.5mm_EP1.6x1.6mm","Texas Instruments","TPA6132A2RTER","https://www.ti.com/lit/ds/symlink/tpa6132a2.pdf","1",""
